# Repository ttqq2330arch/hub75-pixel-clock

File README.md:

# HUB75 Pixel Clock 🕒

ESP32-S3 驱动的 **64×64 HUB75 全彩点阵像素时钟 / 氛围屏**开源固件。
板子自带网页控制台，支持表盘商店、亮度调节、屏幕旋转、WiFi 切换、动画播放，
开机自检 + 软启动供电保护，断网也能靠 NTP 缓存走时。

> HUB75 Pixel Clock — an open-source firmware for a 64×64 HUB75 RGB LED matrix
> clock driven by ESP32-S3, with a built-in web console (watch-face store,
> brightness, screen rotation, WiFi switching, animations).

---

## 📷 实拍展示

| 桌面实拍 · 时钟表盘 | 桌面实拍 · 像素动画场景 |
|---|---|
|  |  |

> 64×64 HUB75 全彩点阵，ESP32-S3 驱动，网页控制台实时切换表盘与动画。

## ✨ 特性

- **64×64 HUB75 全彩点阵**，双缓冲 DMA 驱动，刷新率约 120Hz
- **网页控制台**（`http://<板子IP>/`）：表盘商店 / 亮度滑块 / **屏幕旋转** / **WiFi 切换** / 动画
- **微信小程序控制端**（`miniprogram/`）：手机扫码即用，与网页版共用同一套 API
- **表盘商店**：内置多款表盘，可通过网页上传自定义 `.rgb565` 表盘
- **屏幕旋转**：0°/90°/180°/270° 一键切换，断电保存
- **WiFi 切换**：网页直接改 WiFi，连不上自动回落配网热点，永不失联
- **开机自检 + 供电软启动**：全屏自检亮度压到安全档，2.5s 亮度软爬坡，避免弱供电拉垮
- **NTP 时间同步**（CST-8），断网缓存走时
- **开源驱动参数**：矩阵初始化已对齐 WuyongLab-ESP32S3-PixelClock 同款已验证配置

| 项 | 值 |
|---|---|
| 主控 | ESP32-S3 **N16R8**（16MB Flash + 8MB PSRAM） |
| 屏 | P2.5 64×64 RGB HUB75 全彩点阵（5V/4A 额定，1/32 扫描） |
| 驱动库 | mrfaptastic/ESP32-HUB75-MatrixPanel-I2S-DMA |
| Flash 分区 | `partitions_16mb.csv`：OTA A/B + 表盘存储区 |
| 固件版本 | **v0.3.23** |

---

## ⚠️ 供电红线（先读再接线，不然烧板）

P2.5 全线密度高，全白实测可达 **4A 以上**。**严禁**从 ESP32 开发板 USB/VIN 取电给屏：

- 电源：独立 **5V/5A** 开关电源
- **供电走屏上的 VH4 插座（+5V/GND）**，排线只走信号
- 电源与屏 GND 必须和 ESP32 GND **共地**
- 屏 VCC/GND 入口并 **1000µF/25V 电解 + 0.1µF 陶瓷** 滤波

> 省钱提示：微雪 ESP32-S3-RGB-Matrix 驱动板（S3 + 排线座 + VH4 供电座三合一）可免飞线。

---

## 🔌 引脚映射（S3 专用，勿套老 ESP32 表）

N16R8 的 GPIO26~37 被 Flash + PSRAM 占用，GPIO19/20 是 USB。本映射已验证。

| HUB75 | GPIO | | HUB75 | GPIO |
|---|---|---|---|---|
| R1 | 4 | | CLK | 13 |
| G1 | 5 | | LAT | 11 |
| B1 | 6 | | OE | 12 |
| R2 | 7 | | A | 17 |
| G2 | 15 | | B | 18 |
| B2 | 16 | | C | 8 |
| | | | D | 9 |
| | | | **E** | **10** |

> E 脚（行扫描 16）**绝不能悬空**——64×64 是 1/32 扫描，缺 E 会上下半屏分裂。

可选外设：GPIO41/42 → SHT30 温湿度；GPIO14 → 蜂鸣器；GPIO0 → BOOT 键（短按切表盘 / 长按 3s 重置 WiFi）。

---

## 🛠️ 编译与烧录

需要 [PlatformIO](https://platformio.org/)（Core + ESP32 平台）：

```bash
cd hub75-pixel-clock
pio run                      # 编译
pio run -t upload            # 烧录（板子插 USB，必要时按住 BOOT 再插）
pio device monitor           # 115200 看启动日志
```

首次编译会自动拉取依赖（ESP32-HUB75-MatrixPanel-I2S-DMA 等）并下载工具链。
自定义板型定义在 `boards/esp32-s3-devkitc-1-n16r8.json`。

---

## 📡 首次配网

板子无 WiFi 凭据时开热点：

1. 手机/电脑连热点 **`PixelClock-Setup`**（密码 **`12345678`**）
2. 浏览器开 **`http://192.168.4.1`**
3. 填家里 WiFi 名称 + 密码 → 保存 → 板子重启连网
4. 开机横幅显示分配到的 IP（也可在路由器后台看设备名 `pixelclock`）

连上后随时访问 **`http://<板子IP>/`** 打开控制台。
> 换 WiFi 不必重刷：控制台「WiFi 切换」直接填，连不上会自动回落此热点。

---

## 🌐 网页控制台 & API 速查

| 功能 | 说明 |
|---|---|
| 表盘商店 | 切换/上传表盘 |
| 屏幕亮度 | 滑块 0–255，应用后保存 |
| **屏幕旋转** | 0°/90°/180°/270° 一键切换，断电保存 |
| **WiFi 切换** | 网页改 WiFi，自动回落热点 |

| 接口 | 方法 | 说明 |
|---|---|---|
| `/status` | GET | 返回 ip / rssi / host / bright / **rot** |
| `/brightness` | GET/POST | 读取/设置亮度（POST `?level=0..255`） |
| `/rotate` | GET/POST | 循环切换 / 指定角度（`?v=0..3`） |
| `/wifi` | GET/POST | 读取当前 SSID / 切换（`?ssid=&pass=`） |
| `/diallist` | GET | 已安装表盘清单 |
| `/faces` | GET | 内置表盘封面（gzip） |

---

## 📱 微信小程序控制端（手机端）

不想开电脑？**用手机浏览器扫码即用**，功能与网页控制台等价。

<p align="center"><sub>↑ 小程序控制台界面（按 <code>miniprogram/</code> 实际 WXML/WXSS 还原的示意图，非真机截图）</sub></p>

### 三大功能

| 页面 | 能力 |
|---|---|
| **控制台** | 设备在线状态 / 信号强度、亮度滑块 + 预设（10/30/60/100%/息屏）、固件表盘切换、flash 动画播放与保存 |
| **表盘库** | 设备内全部表盘网格预览（64×64 像素风）、点击播放、删除、下拉刷新 |
| **表盘商店** | 7 个本地像素表盘，一键推送到设备并立即播放 |

### 快速开始（3 步）

1. **微信开发者工具** → 导入项目 → 选择 `miniprogram/` 目录
   - AppID 已带测试号（`wxd4ef8240f24c46ce`），也可换成你自己的
2. **必须关闭域名校验**（否则打不开局域网 IP）：
   详情 → 本地设置 → 勾选「**不校验合法域名、web-view（域名、TLS 版本以及 HTTPS 证书）**」
3. **编译预览**：手机与板子连**同一个 WiFi**，点「预览」扫码

> 板子地址默认 `192.168.1.52`，在「控制台」页顶部可改，**自动记住**（`storage` 键 `pixelclock_ip`）。

### 技术要点

- **通信**：全部走 WiFi HTTP（`wx.request` → 板子 `WebServer`），与网页版**同一套 API**
  （`/status` `/brightness` `/face` `/diallist` `/dialpreview` `/dialplay` `/dialdel` `/dialup` `/animload` `/animsave`）
- **预览图**：`/dialpreview` 返回首帧 8192B RGB565 小端 base64 → `utils/render.js` 解成 ImageData 画上 canvas 2d
- **上传**：`/dialup` 裸 hex 分块（4096B/块，`Content-Type: text/plain`，`final=1&play=1` 收尾即播）
- **参数约定**：POST 参数一律走 URL query（板子 WebServer 不解析 JSON body）

### ⚠️ 关于蓝牙通道

小程序**当前不提供蓝牙控制**。原因：固件侧 `src/config.h` 的 `ENABLE_BLE=0`（BLE + WiFi 共存会挤爆 lwIP 堆），
`ble_service.cpp` 整块不编译，板子不广播 GATT 服务，扫描必然失败。

代码已完整保留。若你的固件改回 `ENABLE_BLE=1`，把 `miniprogram/pages/home/home.js` 顶部的
`const BLE_ENABLED = false` 改成 `true`，小程序端**无需其他改动**即可复活蓝牙通道。

> 蓝牙模式设计为「体验版免域名通道」——正式版小程序走局域网 IP 需在审核备注里说明是内部运营用途。

### 常见问题

| 现象 | 原因 |
|---|---|
| 小程序一直转圈 / 请求失败 | 90% 是**没关域名校验**，或手机与板子不在同一网段 |
| 改表盘要重新编译吗 | 不用。改 `miniprogram/data/faces/` 后重新导入即可 |
| 想公网控制 | 局域网方案不适用于校外网络，需要内网穿透 / 云方案 |

---

## 📲 Android APP（原生，个人版）

除了网页和微信小程序，还有一套**原生 Android APP**（Kotlin + Jetpack Compose），
可直接侧载安装，**不用上架、不用开发者资质、不用备案**。

| 能力 | 说明 |
|---|---|
| **mDNS 自动发现** | 自动找到局域网里的板子，不用手输 IP；板子换 IP 也不用重填 |
| 控制台 | 在线状态 / 信号强度 / 亮度滑块 / 屏幕旋转 / 表盘商店 / 固件内置表盘 / 远程动画 / WiFi 切换 |
| 表盘库 | 板载表盘真实缩略图网格、播放、删除、推送新 `.rgb565` 表盘到 flash |
| **像素工坊** | 把你的「HUB75 像素图片生成器」直接嵌进 APP（WebView），图片→限色+抖动→像素图，**一键直推设备**，目标设备自动取 APP 已连板子 |
| **叠加时钟位置调整** | 表盘库点「调时钟」，在 64×64 预览图上**直接拖动**叠加的 `HH:MM`；可切样式/字号/颜色/显示开关 |
| 表盘商店 | 6 款单帧表盘（笑脸/爱心/星星/彩虹/数字雨/火焰），点一下推上屏 |
| 隐私 | 全程局域网直连，**不联网、不上传任何数据**、无账号无埋点 |

> 示意图，非真机截图。底图与坐标均取自板子上的真实表盘数据。

工程在 [`app-android/`](app-android/)，构建：

```bash
cd app-android
python build_app.py            # 一键出 APK（自动处理中文路径问题）
python build_app.py --install  # 构建并安装到已连接设备
```

> 明文 HTTP 只对私有网段放行（`network_security_config.xml`），公网域名仍强制 HTTPS。

---

## 📁 代码结构

```
src/
  main.cpp          主循环、任务调度、BOOT 键
  config.h          版本号、功能开关（ENABLE_BLE 等）、引脚/分辨率
  display_mgr.*     HUB75 初始化、自检、亮度软爬坡、旋转坐标变换
  net.cpp           网页服务器、配网门户、全部 REST 接口
  face_*.cpp        表盘（时钟/等离子/遥测/测试）与远程表盘播放
  faces_data.h      内置表盘封面数据
  push_page_gz.h    控制台网页（gzip，由 tools/gen_push_page_gz.py 生成）
  ble_service.*     BLE 服务（代码保留，config.h 默认关闭以省内存）
miniprogram/       微信小程序控制端（原生 WXML/WXSS/JS）
  app.js/app.json   小程序入口与 tabBar 配置
  pages/home/       控制台（设备状态 / 亮度 / 固件表盘 / 动画）
  pages/dials/      设备表盘库
  pages/store/      本地表盘商店
  pages/detail/     表盘详情与推送
  pages/devices/    蓝牙模式（当前固件关闭 BLE，页面有说明）
  utils/api.js      WiFi HTTP 封装（含设备 IP 管理）
  utils/render.js   RGB565 ↔ canvas 渲染
  utils/ble.js      蓝牙通道（保留，固件开 BLE 后启用）
app-android/       原生 Android APP（Kotlin + Jetpack Compose，个人版）
  app/src/main/java/com/ttqq/pixelclock/
    net/BoardClient.kt      板子 HTTP 客户端（全部 REST 接口封装）
    net/BoardDiscovery.kt   mDNS 自动发现 + 网段扫描兜底
    net/DialPreview.kt      base64 → RGB565 像素解码
    ui/                     三页面（控制台/表盘库/设置）+ 组件 + 对话框
  app/src/test/     单元测试 + 真板子联调测试
  build_app.py      一键构建脚本（自动处理中文路径）
  data/faces/       本地像素表盘数据
tools/
  gen_faces_web.py / gen_push_page_gz.py   网页→头文件生成
  flash_firmware.py                     一键烧录脚本
  cap_boot.py / cap_live.py             串口日志抓取
boards/
  esp32-s3-devkitc-1-n16r8.json        自定义板型
```

> 控制台网页改版流程：编辑 `tools/push_page_template.html` →
> `python tools/gen_push_page_gz.py` 重新生成 `src/push_page_gz.h` → 重新编译。

---

## 🙏 致谢

- 矩阵驱动：[mrfaptastic/ESP32-HUB75-MatrixPanel-I2S-DMA](https://github.com/mrfaptastic/ESP32-HUB75-MatrixPanel-I2S-DMA)
- 显示初始化参数参考：[WuyongLab/ESP32S3-PixelClock](https://github.com/WuyongLab/ESP32S3-PixelClock)
  （同硬件点亮验证，本固件驱动/时钟/blanking 参数已对齐其已验证配置）

## 📄 协议

[MIT](LICENSE) — 自由使用、修改、分发。

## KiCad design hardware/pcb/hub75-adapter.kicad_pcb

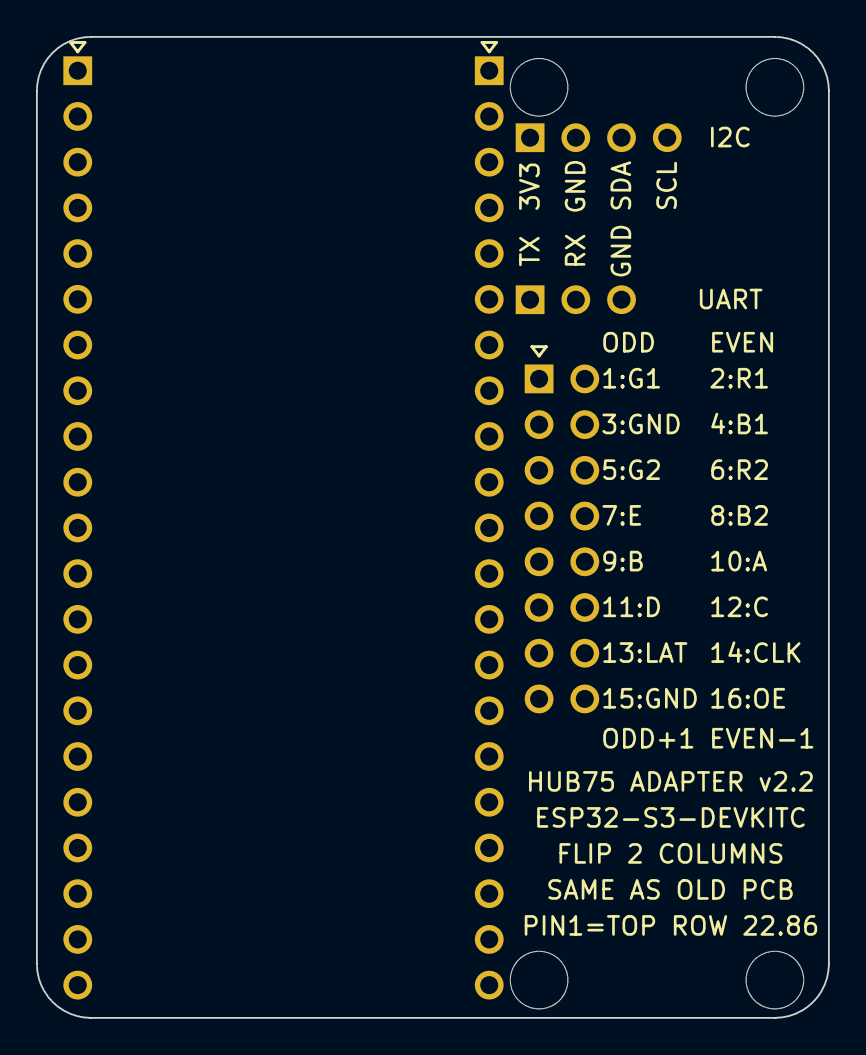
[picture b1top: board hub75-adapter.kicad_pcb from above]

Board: 2 copper layers, 44.0 x 54.5 mm, 9 parts (0 on the bottom side), 20 nets, no tracks yet.

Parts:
H1, H2, H3, H4: MountingHole_3.2mm
J1: Socket_1x22_L
J2: Socket_2x8_HUB75
J3: Socket_1x22_R
J4: PinHeader_1x4
J5: PinHeader_1x3

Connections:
3V3: J1.1, J1.2, J4.1
A: J1.10, J2.10
B: J1.11, J2.9
B1: J1.6, J2.4
B2: J1.9, J2.8
C: J1.12, J2.12
CLK: J1.17, J2.14
D: J1.15, J2.11
E: J1.16, J2.7
G1: J1.5, J2.1
G2: J1.8, J2.5
GND: J2.3, J2.15, J3.1, J3.21, J4.2, J5.3
LAT: J1.18, J2.13
OE: J1.19, J2.16
R1: J1.4, J2.2
R2: J1.7, J2.6
SCL: J3.6, J4.4
SDA: J3.7, J4.3
URX: J3.3, J5.2
UTX: J3.2, J5.1
